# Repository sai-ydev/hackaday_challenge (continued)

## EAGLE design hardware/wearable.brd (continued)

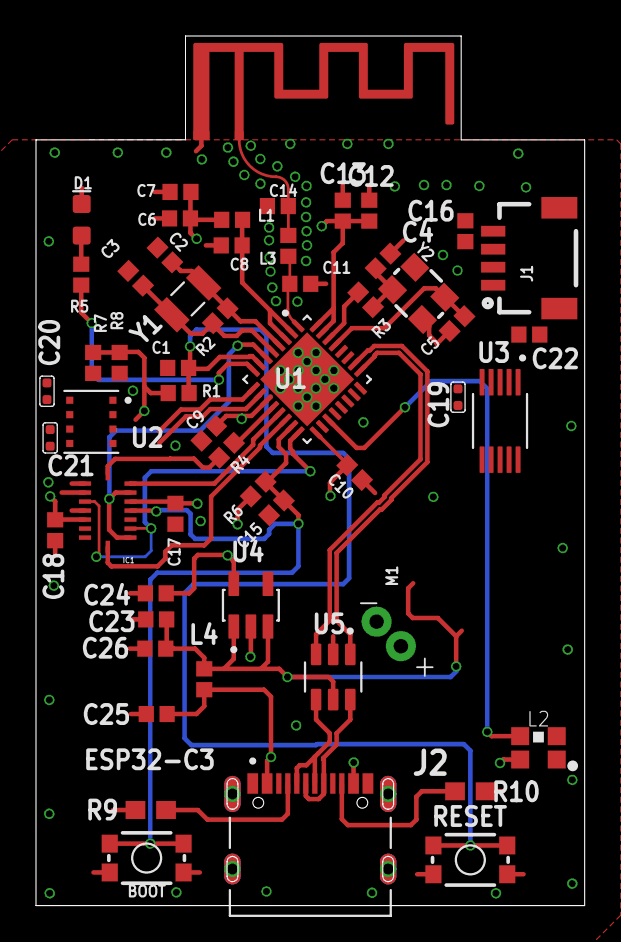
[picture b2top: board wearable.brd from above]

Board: 4 copper layers, 30.5 x 48.3 mm, 55 parts (0 on the bottom side), 34 nets.

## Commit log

2023-05-17 daily check-in
2023-05-17 check-in
2023-05-18 Completed design files
2023-05-18 3D model updates
2023-05-18 Completed design
2023-05-30 Moving files into hardware folder
